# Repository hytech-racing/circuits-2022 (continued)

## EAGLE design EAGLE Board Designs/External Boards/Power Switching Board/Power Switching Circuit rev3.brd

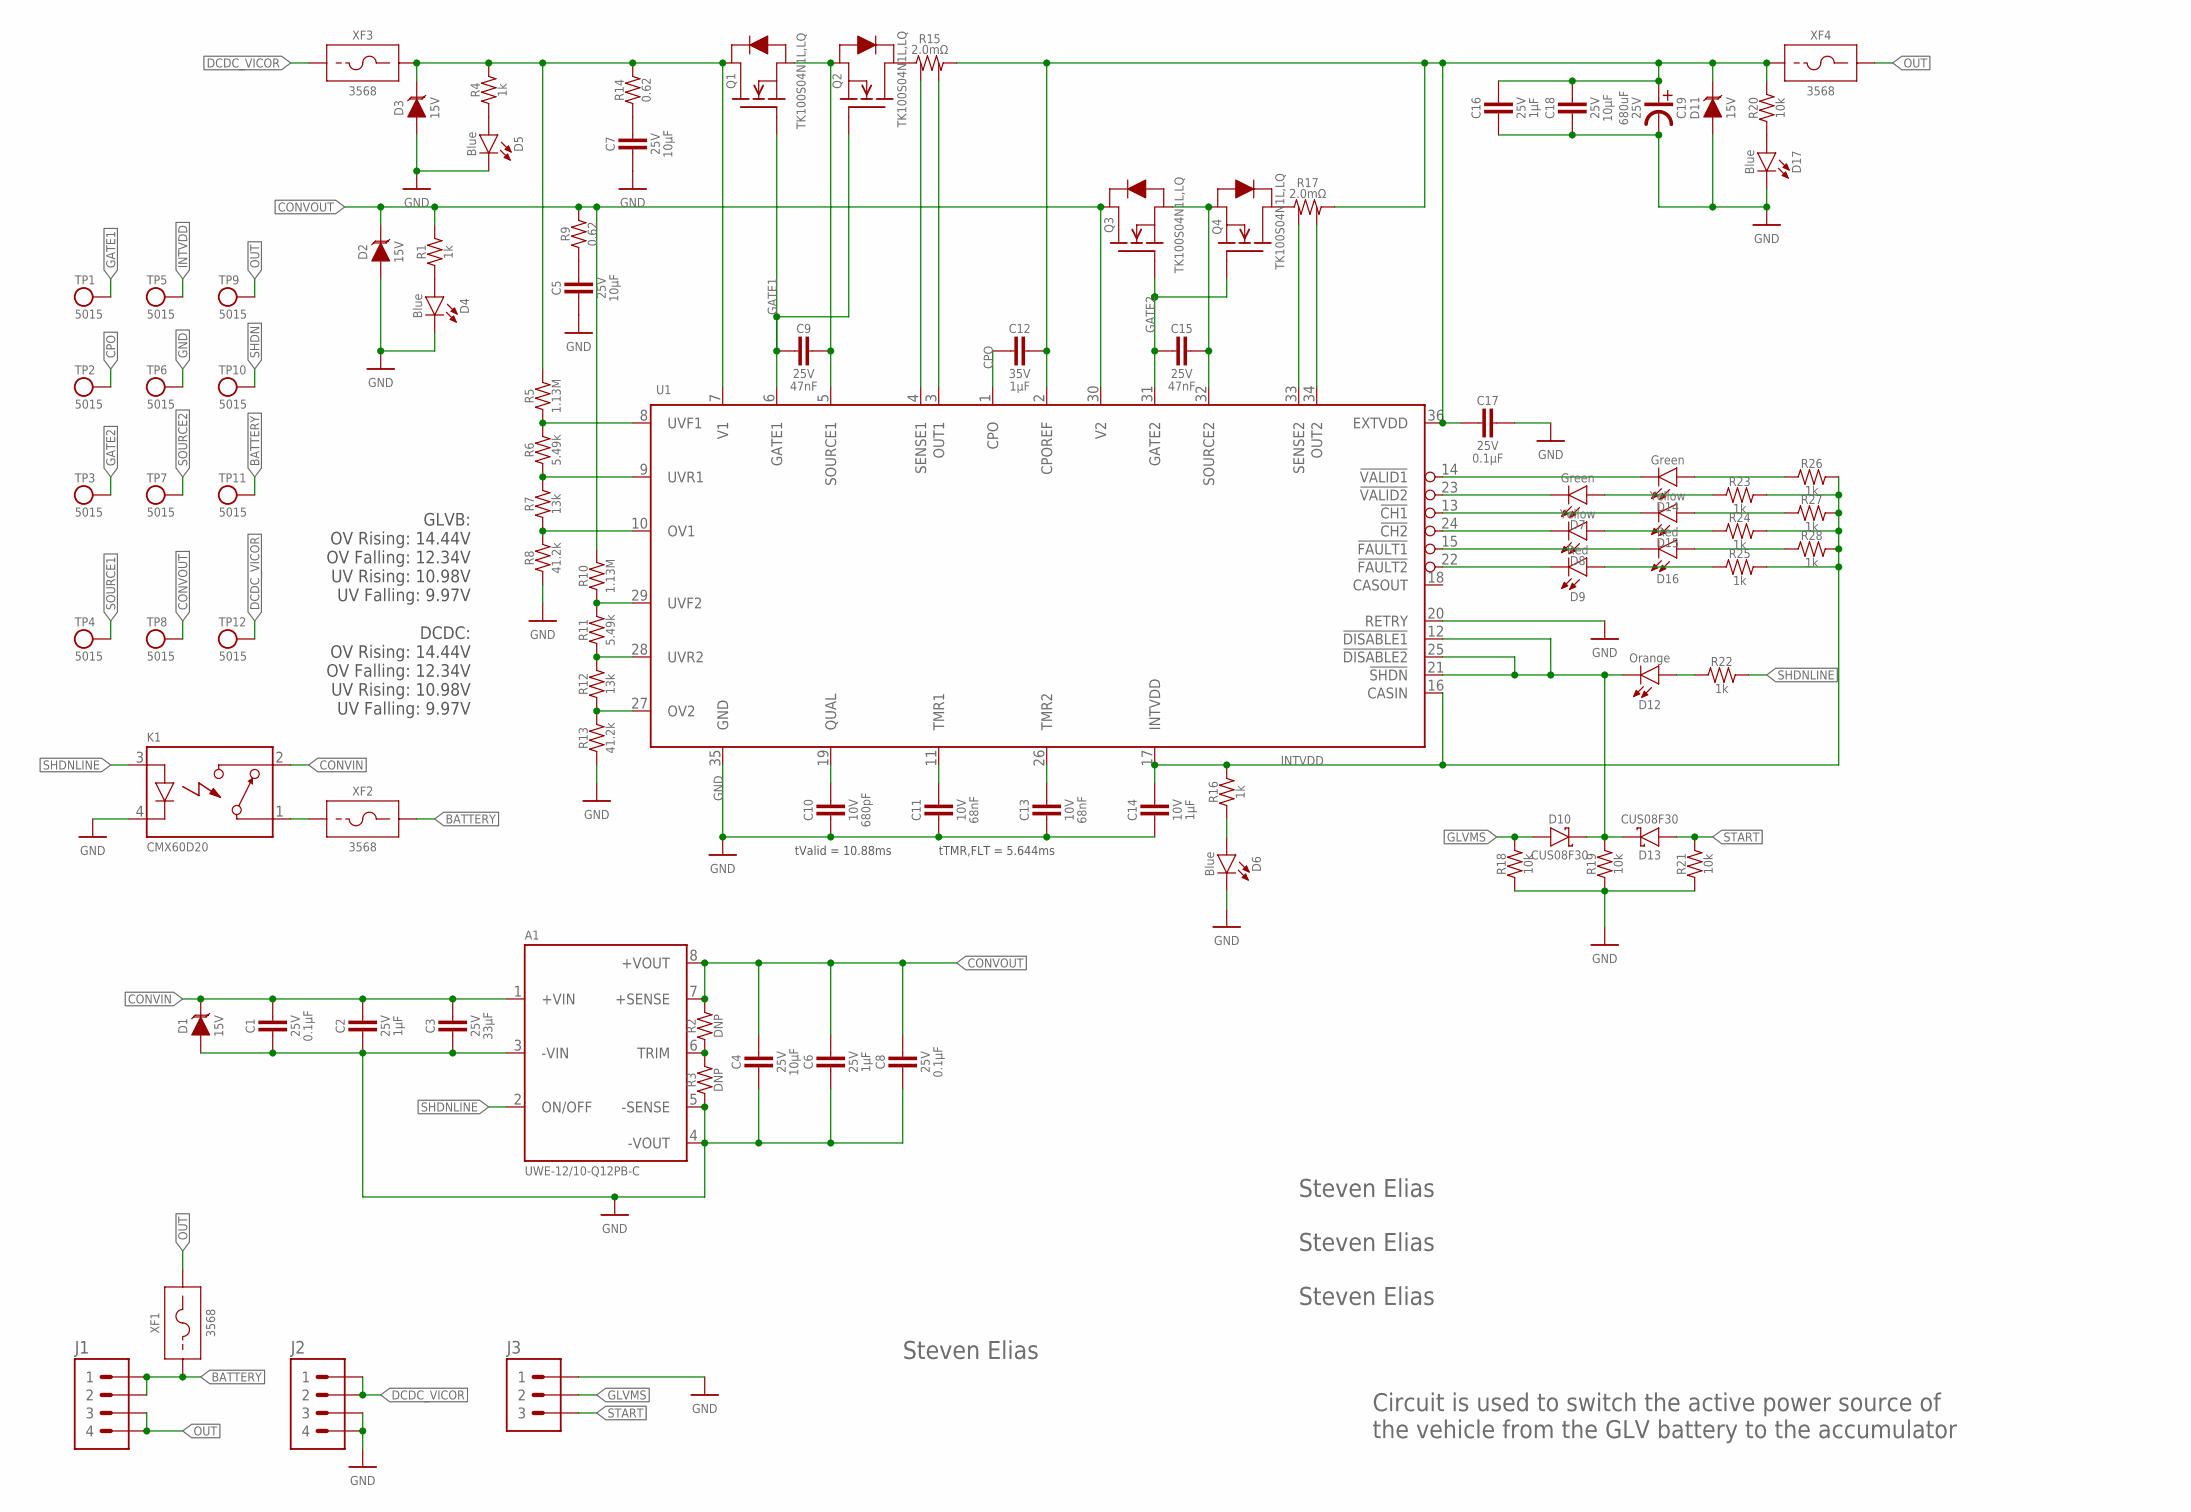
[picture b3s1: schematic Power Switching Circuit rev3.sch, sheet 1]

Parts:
A1: UWE-12/10-Q12PB-C; UWE-*
C1, C8, C17: CAPACITOR_0603_25V_0.1UF; 0603-CAP
C2, C6, C16: CAPACITOR_0603_25V_1UF; 0603-CAP
C3: CAPACITOR_1206_25V_33UF; 1206-CAP
C4, C5, C7, C18: CAPACITOR_0603_25V_10UF; 0603-CAP
C9, C15: CAPACITOR_0603_25V_47NF; 0603-CAP
C10: CAPACITOR_0603_10V_680PF; 0603-CAP
C11, C13: CAPACITOR_0603_10V_68NF; 0603-CAP
C12: CAPACITOR_0603_35V_1UF; 0603-CAP
C14: CAPACITOR_0603_10V_1UF; 0603-CAP
C19: EEUFP1E681; EEUFP1E*
D1, D2, D3, D11: TVS_15V; SOT-23
D4, D5, D6, D17: LED_0603_BLUE; 0603-LED
D7, D14: LED_0603_GREEN; 0603-LED
D8, D15: LED_0603_YELLOW; 0603-LED
D9, D16: LED_0603_RED; 0603-LED
D10, D13: SCHOTTKY_SOD323_30V; SOD-323
D12: LED_0603_ORANGE; 0603-LED
J1, J2: CONNECTOR-4_SOURIAU_; SOURIAU_12-04
J3: CONNECTOR-3_; SOURIAU_04-35
K1: RELAY_SOLIDSTATE_NO_CMX60D20; CRYDOM_CMX
Q1, Q2, Q3, Q4: TRANSISTOR_N_MOS_2-7K1S_TK100S04N1LLQ; DPAK(2-7K1S)
R1, R4, R16, R22, R23, R24, R25, R26, R27, R28: RESISTOR_0603_1K; 0603-RES
R2, R3: RESISTOR_0603_DNP; 0603-RES
R5, R10: RESISTOR_0603_1.13M; 0603-RES
R6, R11: RESISTOR_0603_5.49K; 0603-RES
R7, R12: RESISTOR_0603_13K; 0603-RES
R8, R13: RESISTOR_0603_41.2K; 0603-RES
R9, R14: RESISTOR_0805_0.62; 0805-RES
R15, R17: RESISTOR_SENSE__WSL40262L000FEB; 4026
R18, R19, R20, R21: RESISTOR_0603_10K; 0603-RES
TP1, TP2, TP3, TP4, TP5, TP6, TP7, TP8, TP9, TP10, TP11, TP12: TEST_POINT; 5015
U1: LTC4421; SSOP-36
XF1, XF2, XF3, XF4: FUSE_HOLDER_MINIBLADEPTH; 3568

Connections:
!CH1: D15.1 (C), U1.13 (!CH1)
!CH2: D8.1 (C), U1.24 (!CH2)
!FAULT1: D16.1 (C), U1.15 (!FAULT1)
!FAULT2: D9.1 (C), U1.22 (!FAULT2)
!VALID1: D14.1 (C), U1.14 (!VALID1)
!VALID2: D7.1 (C), U1.23 (!VALID2)
BATTERY: J1.1, J1.2, TP11.1, XF1.1, XF1.2 (1), XF2.3 (2), XF2.4 (2)
CONVIN: A1.1 (+VIN), C1.1, C2.1, C3.1, D1.3 (C), K1.2 (CONTACT2)
CONVOUT: A1.7 (+SENSE), A1.8 (+VOUT), C4.1, C6.1, C8.1, D2.3 (C), Q3.2 (D), R1.2, R2.2, R9.2, R10.2, TP8.1, U1.30 (V2)
CPO: C12.2, TP2.1, U1.1 (CPO)
DCDC_VICOR: J2.1, J2.2, TP12.1, XF3.1, XF3.2 (1)
GATE1: C9.2, Q1.1 (G), Q2.1 (G), TP1.1, U1.6 (GATE1)
GATE2: C15.2, Q3.1 (G), Q4.1 (G), TP3.1, U1.31 (GATE2)
GLVMS: D10.A, J3.B (2), R18.2
GND: A1.3 (-VIN), A1.4 (-VOUT), A1.5 (-SENSE), C1.2, C2.2, C3.2, C4.2, C5.2, C6.2, C7.2, C8.2, C10.2, C11.2, C13.2, C14.2, C16.2, C17.1, C18.2, C19.P$2 (MINUS), D1.1 (A), D2.1 (A), D3.1 (A), D4.1 (C), D5.1 (C), D6.1 (C), D11.1 (A), D17.1 (C), J2.3, J2.4, J3.A (1), K1.4 (CONTROL-), R3.1, R8.1, R13.1, R18.1, R19.1, R21.1, TP6.1, U1.20 (RETRY), U1.35 (GND)
INTVDD: C14.1, R16.2, R23.2, R24.2, R25.2, R26.2, R27.2, R28.2, TP5.1, U1.16 (CASIN), U1.17 (INTVDD)
unnamed: C10.1, U1.19 (QUAL)
unnamed: C11.1, U1.11 (TMR1)
unnamed: C13.1, U1.26 (TMR2)
unnamed: C5.1, R9.1
unnamed: D17.2 (A), R20.1
unnamed: D4.2 (A), R1.1
unnamed: D5.2 (A), R4.1
unnamed: D6.2 (A), R16.1
unnamed: D9.2 (A), R25.1
unnamed: K1.1 (CONTACT1), XF2.1, XF2.2 (1)
unnamed: D16.2 (A), R28.1
unnamed: D8.2 (A), R24.1
unnamed: A1.6 (TRIM), R2.1, R3.2
unnamed: D15.2 (A), R27.1
unnamed: R17.3, U1.33 (SENSE2)
unnamed: D7.2 (A), R23.1
unnamed: R17.4, U1.34 (OUT2)
unnamed: D14.2 (A), R26.1
unnamed: C7.1, R14.1
unnamed: R15.3, U1.4 (SENSE1)
unnamed: R6.1, R7.2, U1.9 (UVR1)
unnamed: R7.1, R8.2, U1.10 (OV1)
unnamed: R10.1, R11.2, U1.29 (UVF2)
unnamed: R11.1, R12.2, U1.28 (UVR2)
unnamed: R12.1, R13.2, U1.27 (OV2)
unnamed: D12.2 (A), R22.1
unnamed: Q4.2 (D), R17.1
unnamed: R15.4, U1.3 (OUT1)
unnamed: Q2.2 (D), R15.1
NET: C12.1, C16.1, C17.2, C18.1, C19.P$1 (PLUS), D11.3 (C), R15.2, R17.2, R20.2, U1.2 (CPOREF), U1.36 (EXTVDD), XF4.1, XF4.2 (1)
NET2: D3.3 (C), Q1.2 (D), R4.2, R5.2, R14.2, U1.7 (V1), XF3.3 (2), XF3.4 (2)
OUT: J1.3, J1.4, TP9.1, XF1.3 (2), XF1.4 (2), XF4.3 (2), XF4.4 (2)
SHDN: D10.C, D12.1 (C), D13.C, R19.2, TP10.1, U1.12 (!DISABLE1), U1.21 (!SHDN), U1.25 (!DISABLE2)
SHDNLINE: A1.2 (ON/OFF), K1.3 (CONTROL+), R22.2
SOURCE1: C9.1, Q1.3 (S), Q2.3 (S), TP4.1, U1.5 (SOURCE1)
SOURCE2: C15.1, Q3.3 (S), Q4.3 (S), TP7.1, U1.32 (SOURCE2)
START: D13.A, J3.C (3), R21.2
UVF1: R5.1, R6.2, U1.8 (UVF1)

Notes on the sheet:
Steven Elias
Circuit is used to switch the active power source of the vehicle from the GLV battery to the accumulator
GLVB: OV Rising: 14.44V OV Falling: 12.34V UV Rising: 10.98V UV Falling: 9.97V DCDC: OV Rising: 14.44V OV Falling: 12.34V UV Rising: 10.98V UV Falling: 9.97V
tValid = 10.88ms
tTMR,FLT = 5.644ms

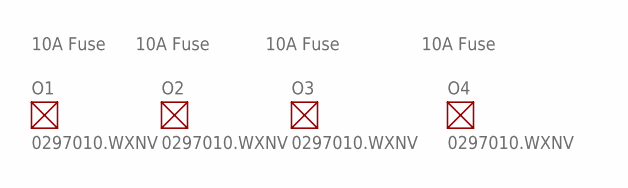
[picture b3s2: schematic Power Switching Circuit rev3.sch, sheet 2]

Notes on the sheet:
10A Fuse

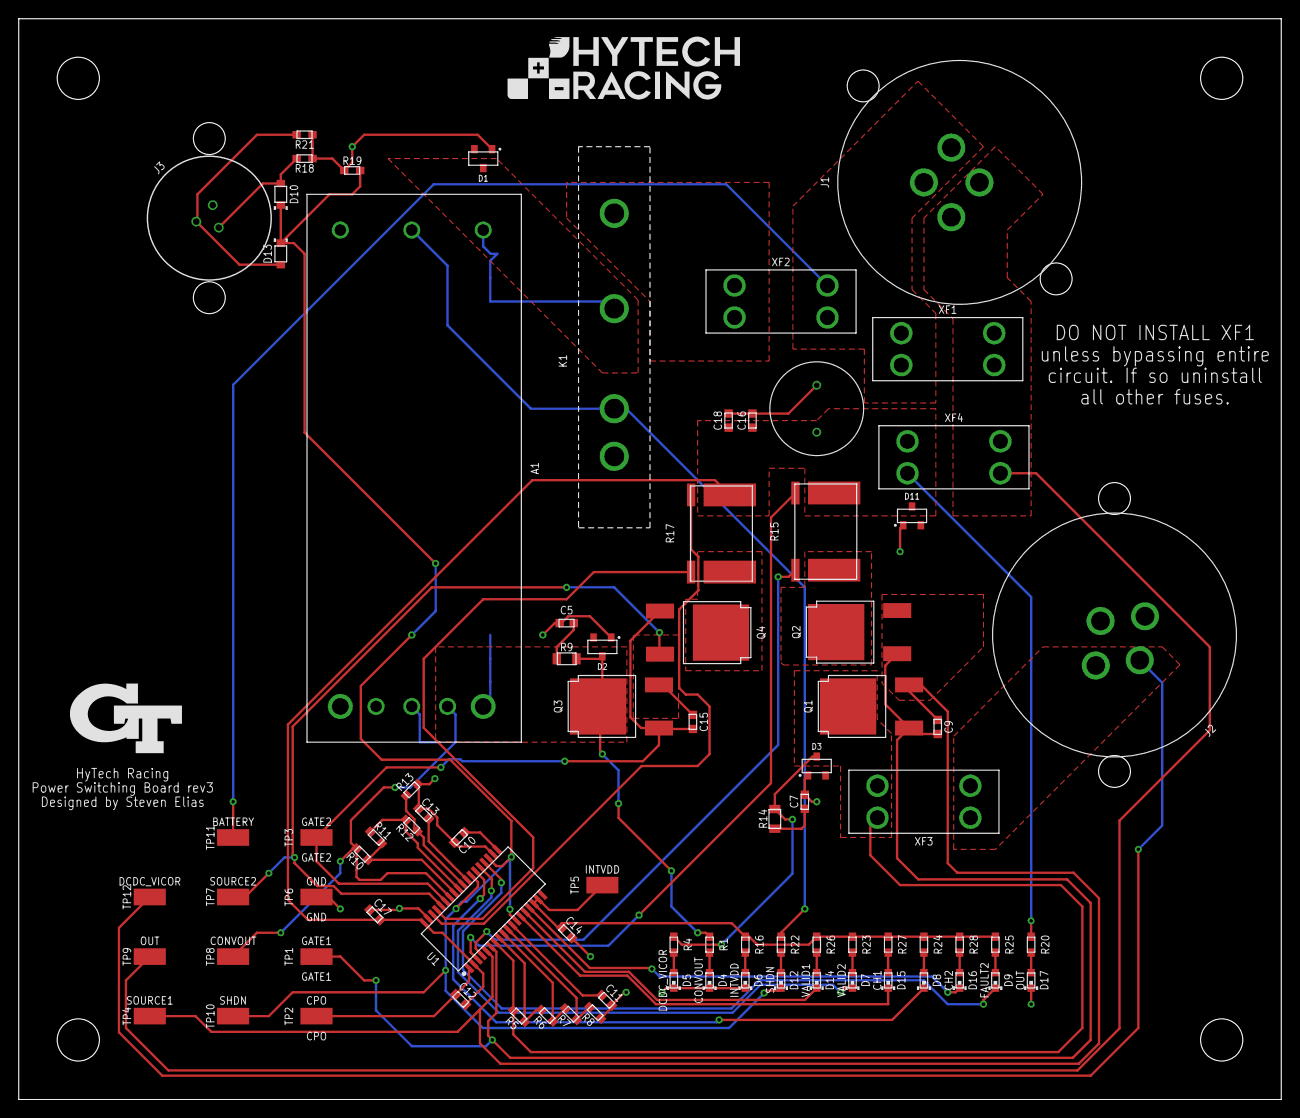
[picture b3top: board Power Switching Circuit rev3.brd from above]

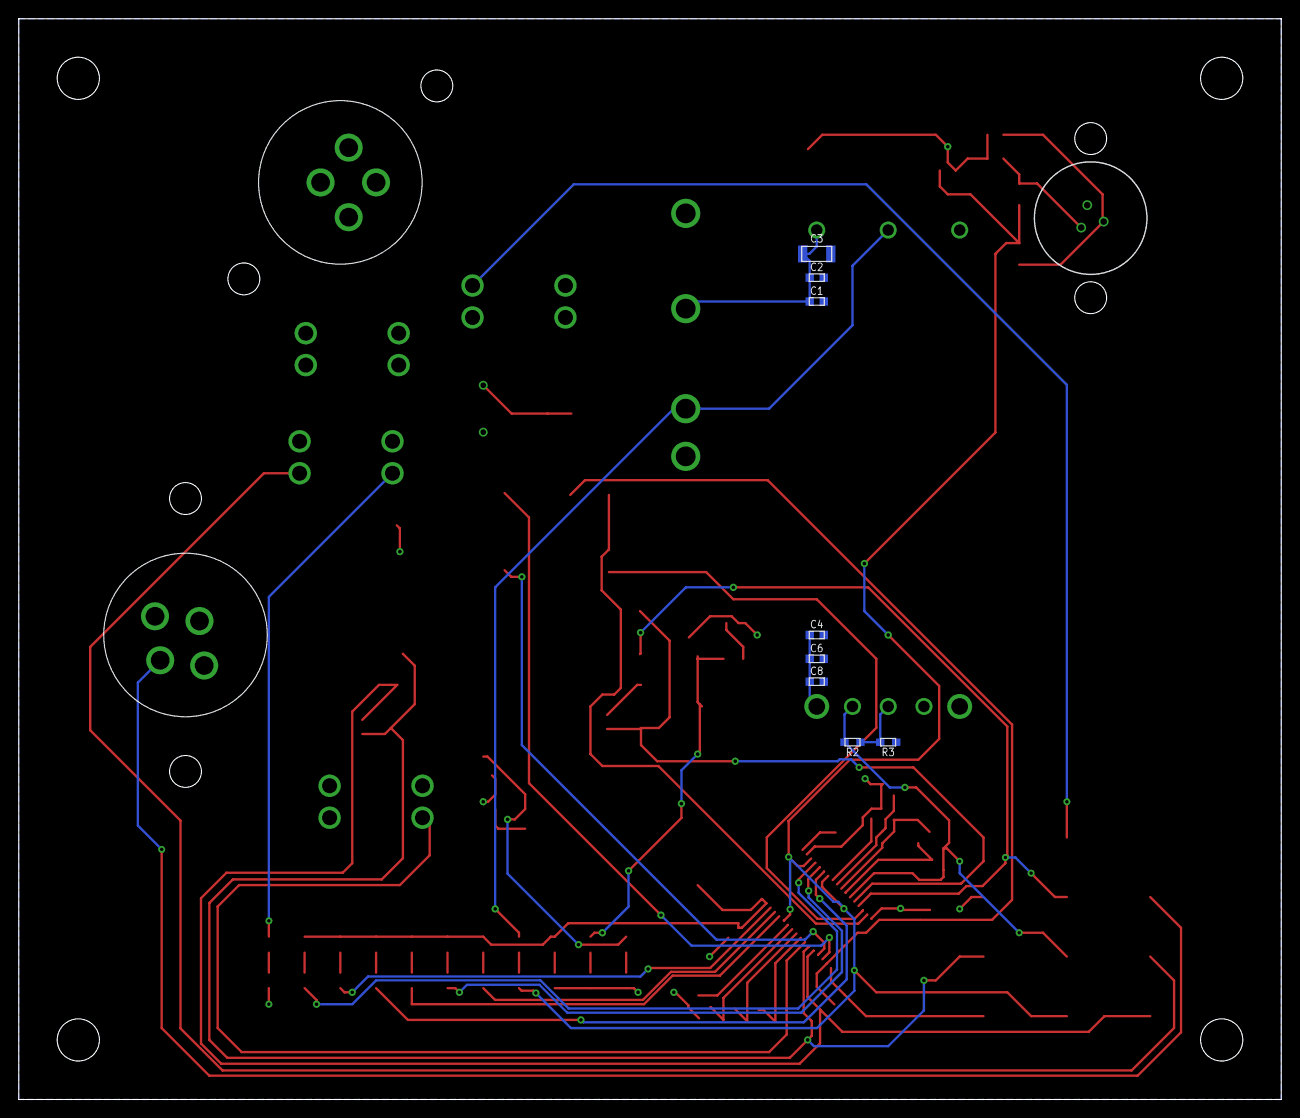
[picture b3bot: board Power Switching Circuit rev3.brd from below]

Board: 2 copper layers, 134.6 x 115.2 mm, 96 parts (8 on the bottom side), 54 nets.

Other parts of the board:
U$1: LOGO_GT_MEDIUM
U$2: LOGO_HYTECH_MEDIUM
U$3, U$4, U$5, U$6: MOUNTING_M4

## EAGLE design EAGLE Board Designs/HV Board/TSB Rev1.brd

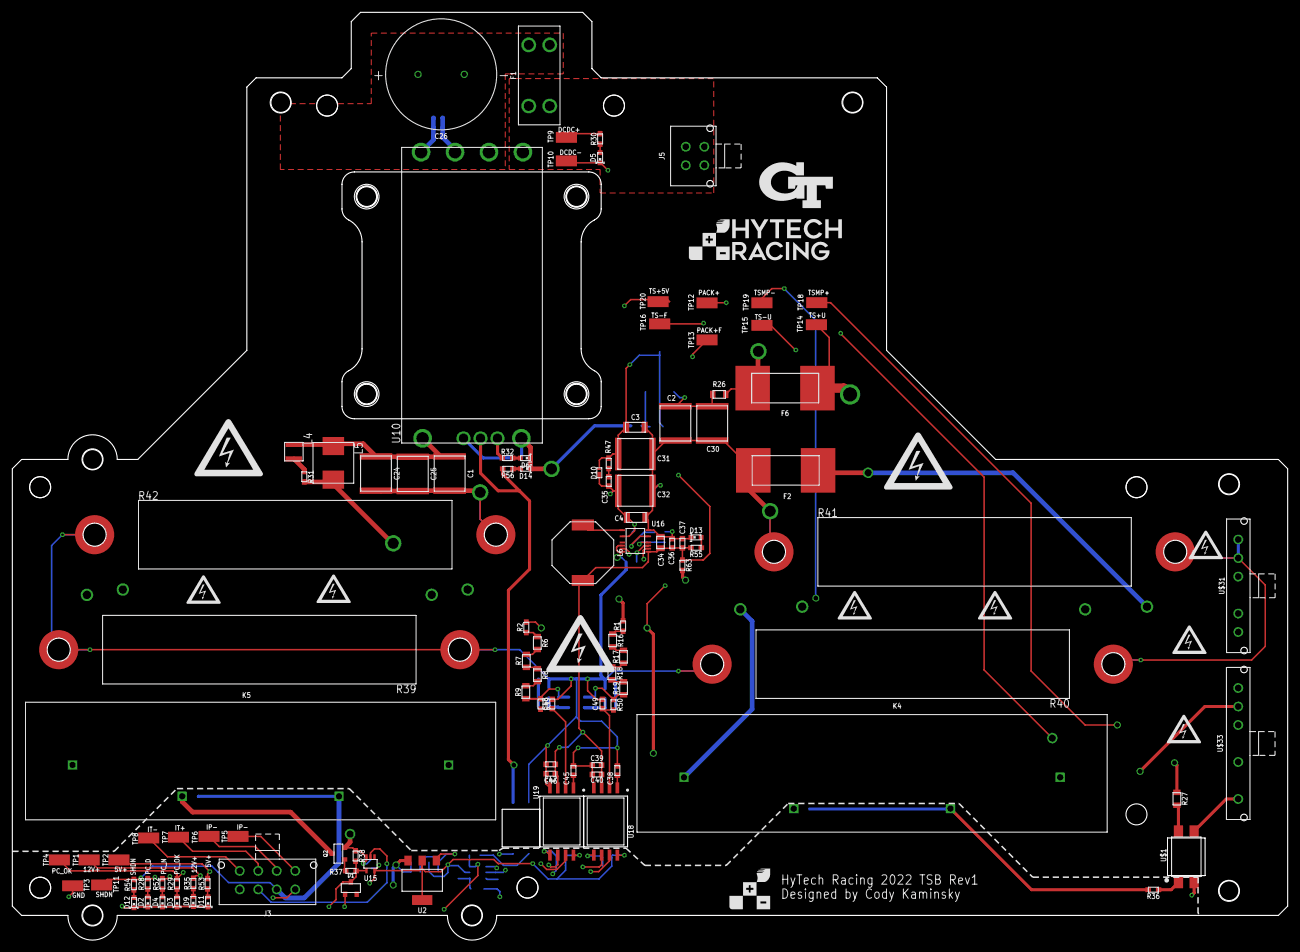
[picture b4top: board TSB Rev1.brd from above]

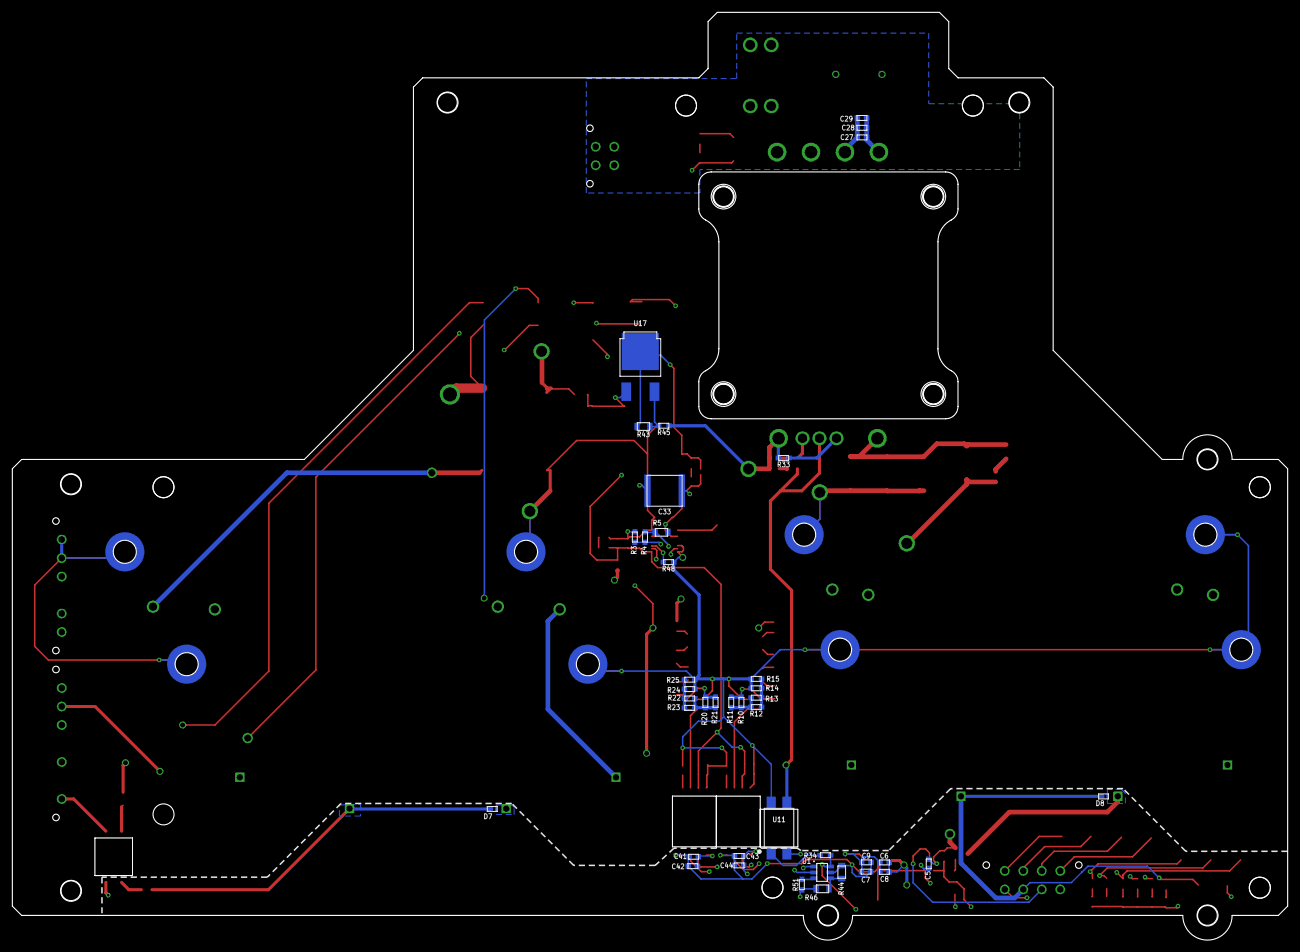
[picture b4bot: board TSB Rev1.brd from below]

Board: 4 copper layers, 206.7 x 150.3 mm, 193 parts (41 on the bottom side), 76 nets.

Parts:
C1, C2: CAPACITOR_2220_630V_0.1UF; 2220-CAP
C3, C4: CAPACITOR_1206_250V_0.1UF; 1206-CAP
C5, C9, C42, C43: CAPACITOR_0603_10V_0.1UF; 0603-CAP
C6, C28, C36: CAPACITOR_0603_25V_1UF; 0603-CAP
C7: CAPACITOR_0603_10V_4.7UF; 0603-CAP
C8, C37: CAPACITOR_0603_25V_0.1UF; 0603-CAP
C24, C25, C30: CAPACITOR_2220_630V_1UF; 2220-CAP
C26: CAPACITOR_POLAR__; EKYC*MM
C27: CAPACITOR_0603_25V_10UF; 0603-CAP
C29: CAPACITOR_0603_35V_0.1UF; 0603-CAP
C31, C32, C33: CAPACITOR_2220_250V_1UF; 2220-CAP
C34: CAPACITOR_0805_25V_22UF; 0805-CAP
C35, C48, C49: CAPACITOR_0603_10V_10NF; 0603-CAP
C38, C39, C40, C41, C44, C45, C46, C47: CAPACITOR_0603_10V_1UF; 0603-CAP
D1: TVS_8V; SOT-23
D2, D14: LED_0603_ORANGE; 0603-LED
D3: LED_0603_YELLOW; 0603-LED
D4: LED_0603_GREEN; 0603-LED
D5, D12: LED_0603_WHITE; 0603-LED
D6: LED_0603_RED; 0603-LED
D7, D8, D10: SCHOTTKY; CLP1608-2L
D9, D11, D13: LED_0603_BLUE; 0603-LED
F1: FUSE__; MINI-BLADE_FUSE_HOLDER
F2, F6: FUSE_0885_1.25; 0885
J3: CONNECTOR-8_MF_T_V_; MOLEX_MICROFIT_PTH_VERTICAL_08_DUAL
J5: CONNECTOR-4__; MOLEX_MICROFIT_PTH_VERTICAL_04_DUAL
K4: RELAY_SPST_NC_POLARIZED_3550_12; 335X
K5: RELAY_SPST_NO_3550_12; 335X
L4: INDUCTOR_PA4334_; PA4334
L5: INDUCTOR_WELMHI_; WE-LMHI
L6: INDUCTOR_SRU1048_330UH; SRU1048
Q2: TRANSISTOR_N_MOS__PMV15ENEA; SOT-23
R1, R2: RESISTOR_0603_5.9K; 0603-RES
R3: RESISTOR_0603_8.66K; 0603-RES
R4: RESISTOR_0603_13K; 0603-RES
R5: RESISTOR_0805_976K; 0805-RES
R6, R7, R8, R9, R16, R17, R18, R19, R43: RESISTOR_0805_365K; 0805-RES
R10, R11, R12, R13, R14, R15, R20, R21, R22, R23, R24, R25, R49, R50: RESISTOR_0603_33.2K; 0603-RES
R26, R27: RESISTOR_0805_1; 0805-RES
R28, R29, R30, R32, R34, R35, R36, R52, R53, R54, R55, R56, R63: RESISTOR_0603_1K; 0603-RES
R31: RESISTOR_0603_1.62; 0603-RES
R33: RESISTOR_0603_DNP; 0603-RES
R37: RESISTOR_0603_10; 0603-RES
R38, R47: RESISTOR_0603_10K; 0603-RES
R39: RESISTOR_GND_1.24K; B20
R40, R41, R42: RESISTOR_GND_10K; B20
R44: RESISTOR_0805_1M; 0805-RES
R45: RESISTOR_0603_3.32K; 0603-RES
R46: RESISTOR_0805_523K; 0805-RES
R48: RESISTOR_0603_75K; 0603-RES
R51: RESISTOR_0603_154K; 0603-RES
TP1, TP2, TP3, TP4, TP5, TP6, TP7, TP8, TP9, TP10, TP11, TP12, TP13, TP14, TP15, TP16, TP18, TP19, TP20: TEST_POINT; MICRO_MINIATURE
U1: LTC6994_1; SOT-23-6
U2: VOLTAGE_REGULATOR_SOT223_5V; SOT223
U10: DCM4623TD2J13D0T70; DCM4623
U11: RELAY_SOLIDSTATE_NC_AG; DIP-4_AIRGAP
U15: LOGICGATE_INVERTER_DCKR; SC-70-5
U16: LTC3639; MSE16(12)
U17: VOLTAGE_REGULATOR_ADJ_LR8_DPAK; DPAK(2-7K1S)
U18, U19: ISO224B_AIRGAP; SOIC-08(WIDE,0.295")-AIRGAP
U$1: RELAY_SOLIDSTATE_NO_AG; DIP-4_AIRGAP
U$5, U$6, U$7, U$8, U$9, U$10, U$11, U$12, U$13, U$14, U$15, U$26, U$34, U$35, U$37, U$38, U$39, U$41: MOUNTING_M3
U$31: CONNECTOR-5_6_SPACED_; MOLEX_MICROFIT_PTH_VERTICAL_06_SINGLE_SPACED
U$33: CONNECTOR-5_7_SPACED_; MOLEX_MICROFIT_PTH_VERTICAL_07_DUAL_SPACED
U$43, U$44, U$45, U$46, U$47, U$49, U$50: HV_0.50"
U$48, U$51, U$52: HV_1.00"
U$53: LOGO_HYTECH_1.0"
U$54: LOGO_GT_0.50"
U$55: LOGO_HYTECH_SQUARE_0.28"
U$56, U$57, U$58, U$59, U$60, U$61, U$62: GLV
U$63, U$64, U$65, U$66, U$67, U$68, U$69: TS

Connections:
+5V: C5.1, C7.1, C9.1, C41.1, C42.1, C43.1, C44.1, R44.2, R53.1, TP2.1, U1.5, U2.2, U2.4, U15.5, U18.8, U19.8
+12V: C6.1, C8.1, J3.1, R35.2, TP1.1, U2.3
DCDC+: F1.L1, F1.L2, J5.1, J5.3, R30.2, TP9.1
DCDC-: C26.-, C27.1, C28.1, C29.1, D5.1, J5.2, J5.4, TP10.1, U10.7, U10.9
ENABLE: R56.2, U10.3, U11.4
GND: C5.2, C6.2, C7.2, C8.2, C9.2, C41.2, C42.2, C43.2, C44.2, D1.1, D2.1, D3.1, D4.1, D7.2, D9.1, D11.1, D12.1, J3.4, K4.3, Q2.2, R38.1, R46.1, R51.1, TP3.1, U1.2, U2.1, U11.2, U15.3, U18.5, U19.5, U$1.2
IP+: J3.5, TP5.1, U19.7
IP-: J3.6, TP6.1, U19.6
IT+: J3.7, TP7.1, U18.7
IT-: J3.8, TP8.1, U18.6
LED+: R63.2, U$31.3
unnamed: D14.2, R56.1
unnamed: R3.2, R4.1, U16.12
unnamed: Q2.1, R37.2
unnamed: R44.1, R46.2, U1.6
unnamed: R4.2, R5.1, U16.14
unnamed: R34.2, U11.1
unnamed: R6.2, R7.2
unnamed: R7.1, R8.1
unnamed: R1.1, R16.1
unnamed: R2.1, R6.1
unnamed: R8.2, R9.2
unnamed: R20.1, R21.1, R22.2, R23.2
unnamed: R9.1, R10.2, R11.2, R49.1
unnamed: R51.2, U1.3
unnamed: C2.1, C30.1, R26.2, U17.1
unnamed: R28.2, R34.1, U1.4
unnamed: D2.2, R28.1
unnamed: D5.2, R30.1
unnamed: R16.2, R17.2
unnamed: R17.1, R18.1
unnamed: R18.2, R19.2
unnamed: D3.2, R29.1
unnamed: R19.1, R20.2, R21.2, R50.1
unnamed: D4.2, R52.1
unnamed: D9.2, R35.1
unnamed: L4.2, R31.1
unnamed: D11.2, R53.2
unnamed: D12.2, R54.1
unnamed: R12.1, R13.1, R14.2, R15.2
unnamed: R22.1, R23.1, R24.2, R25.2
unnamed: R10.1, R11.1, R12.2, R13.2
unnamed: D13.2, R55.1
unnamed: C1.1, C24.1, C25.1, L4.1, L5.1, U10.1
unnamed: D8.2, K5.3, Q2.3
unnamed: D6.2, R32.2
unnamed: R32.1, U10.4
unnamed: R33.1, U10.2
unnamed: C26.+, C27.2, C28.2, C29.2, F1.R1, F1.R2, U10.6, U10.8
unnamed: K5.4, R39.1
unnamed: K4.4, R40.1
unnamed: D1.3, R37.1, R38.2, R52.2, U15.4
unnamed: R36.1, U$1.1
unnamed: R43.1, R45.2, U17.3
unnamed: R27.2, U$1.3
unnamed: C3.1, C31.1, D10.2, R43.2, R47.1, U17.2
unnamed: C35.2, R47.2
unnamed: C4.1, C32.1, C33.1, C35.1, D10.1, R5.2, U16.3
unnamed: C48.1, R49.2, U19.2
unnamed: C49.1, R50.2, U18.2
unnamed: R48.2, U16.11
unnamed: L6.1, U16.1
unnamed: C45.1, U19.1
unnamed: C38.1, U18.1
unnamed: U16.7, U16.10
PACK+: K5.1, TP12.1, U$1.4, U$33.5
PACK+FUSED: R2.2, R27.1, TP13.1
PRECHARGE_OK: J3.3, R29.2, TP4.1, U1.1, U15.2
SHDN: D7.1, D8.1, J3.2, K4.2, K5.2, R36.2, R54.2, TP11.1
TS+5V: C34.1, C36.1, C37.1, C39.1, C40.1, C46.1, C47.1, L6.2, R55.2, R63.1, TP20.1, U16.9, U18.3, U19.3
TS+FUSED: F6.2, L5.2, R1.2, R26.1, R31.2, U$33.4
TS+UNFUSED: F6.1, K4.1, R39.2, R42.1, TP14.1, U$33.1, U$33.2
TS-FUSED: C1.2, C2.2, C3.2, C4.2, C24.2, C25.2, C30.2, C31.2, C32.2, C33.2, C34.2, C36.2, C37.2, C38.2, C39.2, C40.2, C45.2, C46.2, C47.2, C48.2, C49.2, D6.1, D13.1, D14.1, F2.2, R3.1, R14.1, R15.1, R24.1, R25.1, R33.2, R39.3, R39.4, R39.5, R39.6, R40.3, R40.4, R40.5, R40.6, R41.3, R41.4, R41.5, R41.6, R42.3, R42.4, R42.5, R42.6, R45.1, R48.1, TP16.1, U10.5, U11.3, U16.6, U16.8, U16.16, U18.4, U19.4, U$31.1, U$31.2
TS-UNFUSED: F2.1, R40.2, R41.1, TP15.1, U$31.5
TSMP+: R42.2, TP18.1, U$33.3
TSMP-: R41.2, TP19.1, U$31.4

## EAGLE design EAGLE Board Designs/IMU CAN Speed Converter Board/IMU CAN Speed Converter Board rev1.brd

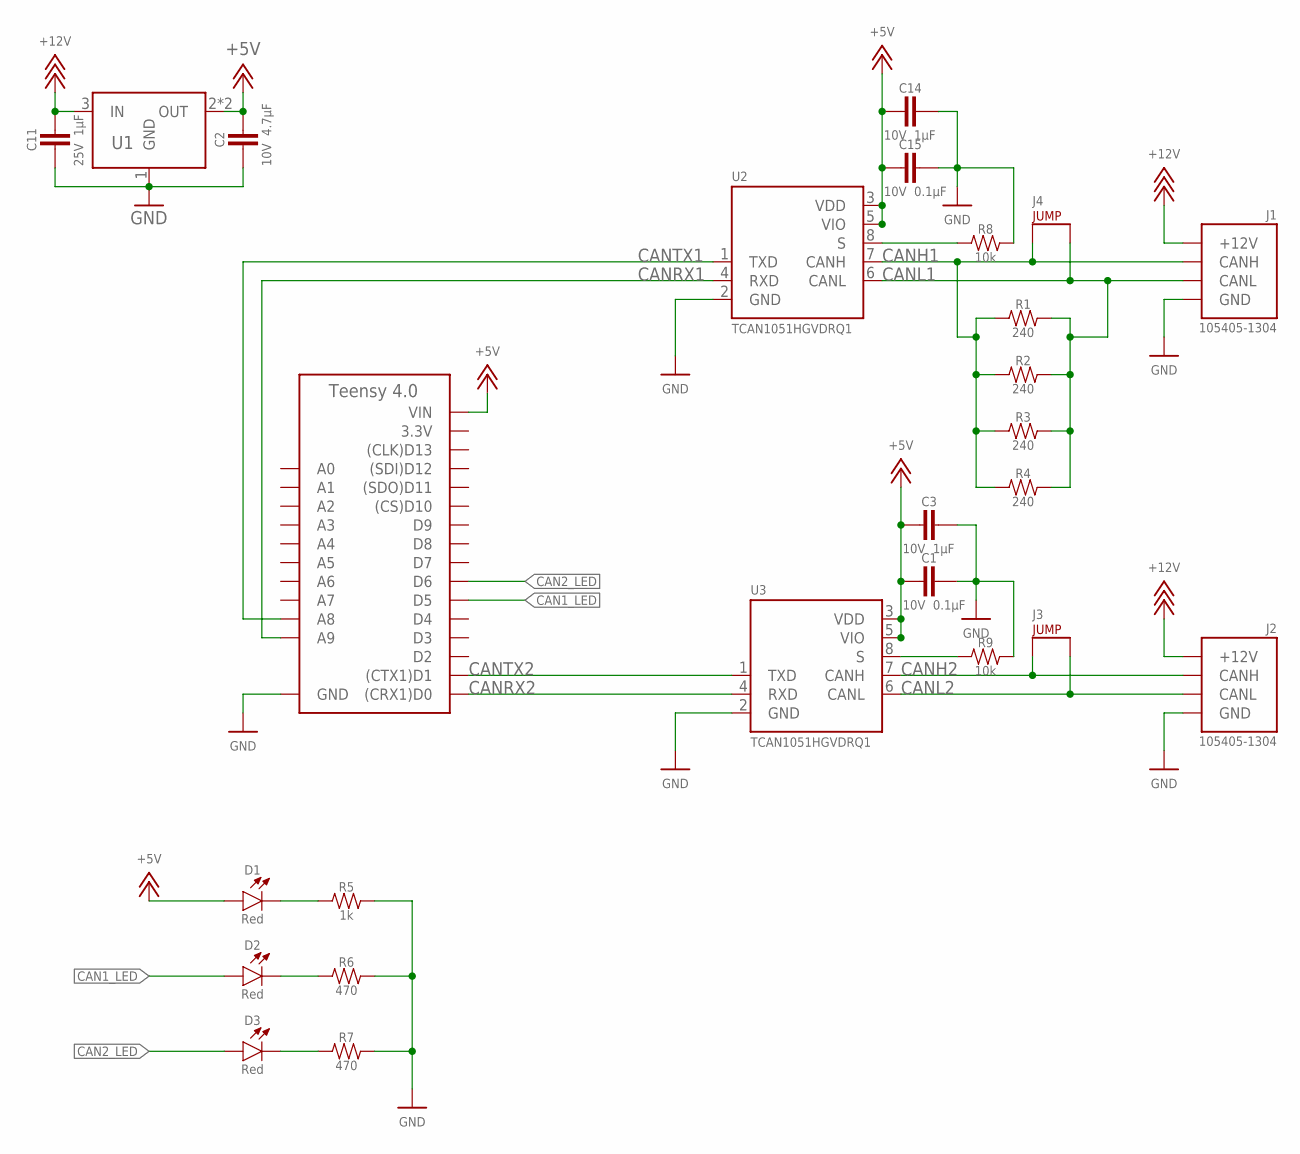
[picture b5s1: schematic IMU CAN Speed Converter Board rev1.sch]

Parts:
A1: TEENSY_4.0; TEENSY_SHORT
C1, C15: CAPACITOR_0603_10V_0.1UF; 0603-CAP
C2: CAPACITOR_0603_10V_4.7UF; 0603-CAP
C3, C14: CAPACITOR_0603_10V_1UF; 0603-CAP
C11: CAPACITOR_0603_25V_1UF; 0603-CAP
D1, D2, D3: LED_0603_RED; 0603-LED
J1, J2: CONNECTOR-CAN_NF_S_RA_BLACK; MOLEX_NANOFIT_SMD_RIGHTANGLE_04
J3, J4: JUMPER_1X02_; 1X02
R1, R2, R3, R4: RESISTOR_0603_240; 0603-RES
R5: RESISTOR_0603_1K; 0603-RES
R6, R7: RESISTOR_0603_470; 0603-RES
R8, R9: RESISTOR_0603_10K; 0603-RES
U1: VOLTAGE_REGULATOR_SOT223_5V; SOT223
U2, U3: TCAN1051HQV-Q1; SOIC-08(NARROW,0.15")

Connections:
3.3V: A1.3.3V
+5V: A1.VIN, C1.2, C2.1, C3.2, C14.2, C15.2, D1.2 (A), U1.2 (OUT), U1.4 (OUT), U2.3 (VDD), U2.5 (VIO), U3.3 (VDD), U3.5 (VIO)
+12V: C11.1, J1.1 (+12V), J2.1 (+12V), U1.3 (IN)
CAN1_LED: A1.D5, D2.2 (A)
CAN2_LED: A1.D6, D3.2 (A)
CANH1: J1.4 (CANH), J4.1, R1.1, R2.1, R3.1, R4.1, U2.7 (CANH)
CANH2: J2.4 (CANH), J3.1, U3.7 (CANH)
CANL1: J1.3 (CANL), J4.2, R1.2, R2.2, R3.2, R4.2, U2.6 (CANL)
CANL2: J2.3 (CANL), J3.2, U3.6 (CANL)
CANRX1: A1.D23 (A9), U2.4 (RXD)
CANRX2: A1.D0 ((CRX1)D0), U3.4 (RXD)
CANTX1: A1.D22 (A8), U2.1 (TXD)
CANTX2: A1.D1 ((CTX1)D1), U3.1 (TXD)
GND: A1.AGND/GND (GND), A1.GND, C1.1, C2.2, C3.1, C11.2, C14.1, C15.1, J1.2 (GND), J2.2 (GND), R5.2, R6.2, R7.2, R8.2, R9.2, U1.1 (GND), U2.2 (GND), U3.2 (GND)
unnamed: D1.1 (C), R5.1
unnamed: D2.1 (C), R6.1
unnamed: D3.1 (C), R7.1
unnamed: R9.1, U3.8 (S)
unnamed: R8.1, U2.8 (S)

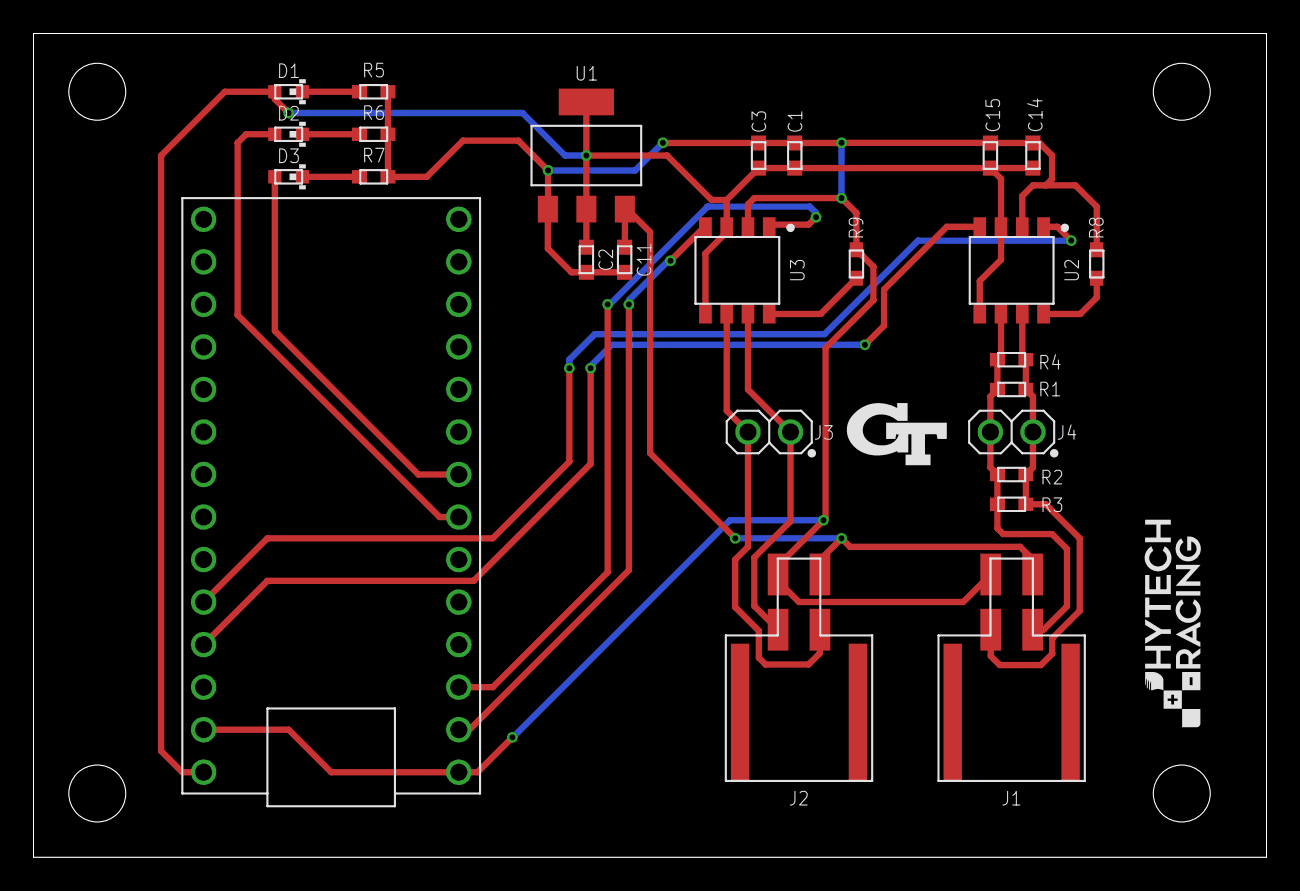
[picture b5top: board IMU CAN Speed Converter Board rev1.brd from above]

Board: 2 copper layers, 73.6 x 49.2 mm, 32 parts (0 on the bottom side), 18 nets.

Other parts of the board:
U$1, U$2, U$4, U$5: MOUNTING_M3
U$3: LOGO_HYTECH_0.5"
U$6: LOGO_GT_0.25"

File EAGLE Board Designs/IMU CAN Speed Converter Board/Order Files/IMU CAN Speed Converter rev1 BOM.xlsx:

Qty | Value | Device | Package | Parts | Description | CAPACITANCE | COLOR | DKPN | MANUFACTURER | MOPN | MPN | POWER | RESISTANCE | TOLERANCE | VOLTAGE | VOLTAGE_CONTINUOUS | VOLTAGE_MAX | Column1
2 | CAPACITOR_0603_10V_0.1UF | CAPACITOR_0603_10V_0.1UF | 0603-CAP | C1, C15 | Capacitor, Non-Polarized | 0.1ÂµF |  | 720-1688-1-ND | Vishay Vitramon | 77-VJ0603Y104JXQPBC | VJ0603Y104JXQPW1BC |  |  | 0.05 | 10V
2 | CAPACITOR_0603_10V_1UF | CAPACITOR_0603_10V_1UF | 0603-CAP | C3, C14 | Capacitor, Non-Polarized | 1ÂµF |  | 311-1796-1-ND | Yageo | 603-CC603KRX7R6BB105 | CC0603KRX7R6BB105 |  |  | 0.1 | 10V
1 | CAPACITOR_0603_10V_4.7UF | CAPACITOR_0603_10V_4.7UF | 0603-CAP | C2 | Capacitor, Non-Polarized | 4.7ÂµF |  | 1276-1044-1-ND | Samsung Electro-Mechanics | 187-CL10A475KP8NNNC | CL10A475KP8NNNC |  |  | 0.1 | 10V
1 | CAPACITOR_0603_25V_1UF | CAPACITOR_0603_25V_1UF | 0603-CAP | C11 | Capacitor, Non-Polarized | 1ÂµF |  | 1276-1184-1-ND | Samsung Electro-Mechanics | 187-CL10B105KA8NNNC | CL10B105KA8NNNC |  |  | 0.1 | 25V
2 | CONNECTOR-CAN_NF_S_RA_BLACK | CONNECTOR-CAN_NF_S_RA_BLACK | MOLEX_NANOFIT_SMD_RIGHTANGLE_04 | J1, J2 | HyTech CAN Connector |  |  |  | Molex |  | 105405-1304
2 | JUMPER_1X02_ | JUMPER_1X02_ | 1X02 | J3, J4 | 2 Pin Connector
3 | LED_0603_RED | LED_0603_RED | 0603-LED | D1, D2, D3 | LED |  | Red | 754-1786-1-ND | Kingbright | 604-APT1608SECKJ3PRV | APT1608SECK/J3-PRV
2 | RESISTOR_0603_10K | RESISTOR_0603_10K | 0603-RES | R8, R9 | Resistor |  |  | 311-10.0KHRCT-ND | Yageo | 603-RC0603FR-0710KL | RC0603FR-0710KL | 0.1W | 10k | 0.01 |  | 31.62V | 75V
1 | RESISTOR_0603_1K | RESISTOR_0603_1K | 0603-RES | R5 | Resistor |  |  | 311-1.00KHRCT-ND | Yageo | 603-RC0603FR-071KL | RC0603FR-071KL | 0.1W | 1k | 0.01 |  | 10.00V | 75V
4 | RESISTOR_0603_240 | RESISTOR_0603_240 | 0603-RES | R1, R2, R3, R4 | Resistor |  |  | 311-240HRCT-ND | Yageo | 603-RC0603FR-07240RL | RC0603FR-07240RL | 0.1W | 240 | 0.01 |  | 4.90V | 75V
2 | RESISTOR_0603_470 | RESISTOR_0603_470 | 0603-RES | R6, R7 | Resistor |  |  | P470BYCT-ND | Panasonic Electronic Components | 667-ERJ-PA3F4700V | ERJ-PA3F4700V | 0.25W | 470 | 0.01 |  | 10.84V | 150V
2 | TCAN1051HQV-Q1 | TCAN1051HQV-Q1 | SOIC-08(NARROW,0.15)" | U2, U3 | TCAN1051*V Can Tranciever |  |  | 296-49935-1-ND | Texas Instruments | 595-TCAN1051HGVDQ1 | TCAN1051HGVDRQ1
1 | TEENSY_4.0 | TEENSY_4.0 | TEENSY_SHORT | A1 | Teensy 4.0
1 | VOLTAGE_REGULATOR_SOT223_5V | VOLTAGE_REGULATOR_SOT223_5V | SOT223 | U1 | Voltage Regulators |  |  | 497-17240-1-ND | STMicroelectronics | 511-LDL1117S50R | LDL1117S50R
